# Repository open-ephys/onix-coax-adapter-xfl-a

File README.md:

# ONIX X.Coax Adapter Boards
Coaxial micro-tether interface for the following headstages and miniscopes

| Revision | Compatibility | Status |
|-|-|-|
| X.FL\rev1.0 | Headstage-64 | Produced and validated |
| X.FL\rev1.1 | Headstage-64 | Not produced |
| X.FL\rev1.2 | Headstage-64 | Produced and validated |
| X.FL\rev2.0 | Headstage-64s <br /> Headstage-16Stim <br /> Headstage-RHS2116 <br /> Kiloscope | Produced and validated |
| U.FL\rev1.0 | Headstage-64 | Not produced |

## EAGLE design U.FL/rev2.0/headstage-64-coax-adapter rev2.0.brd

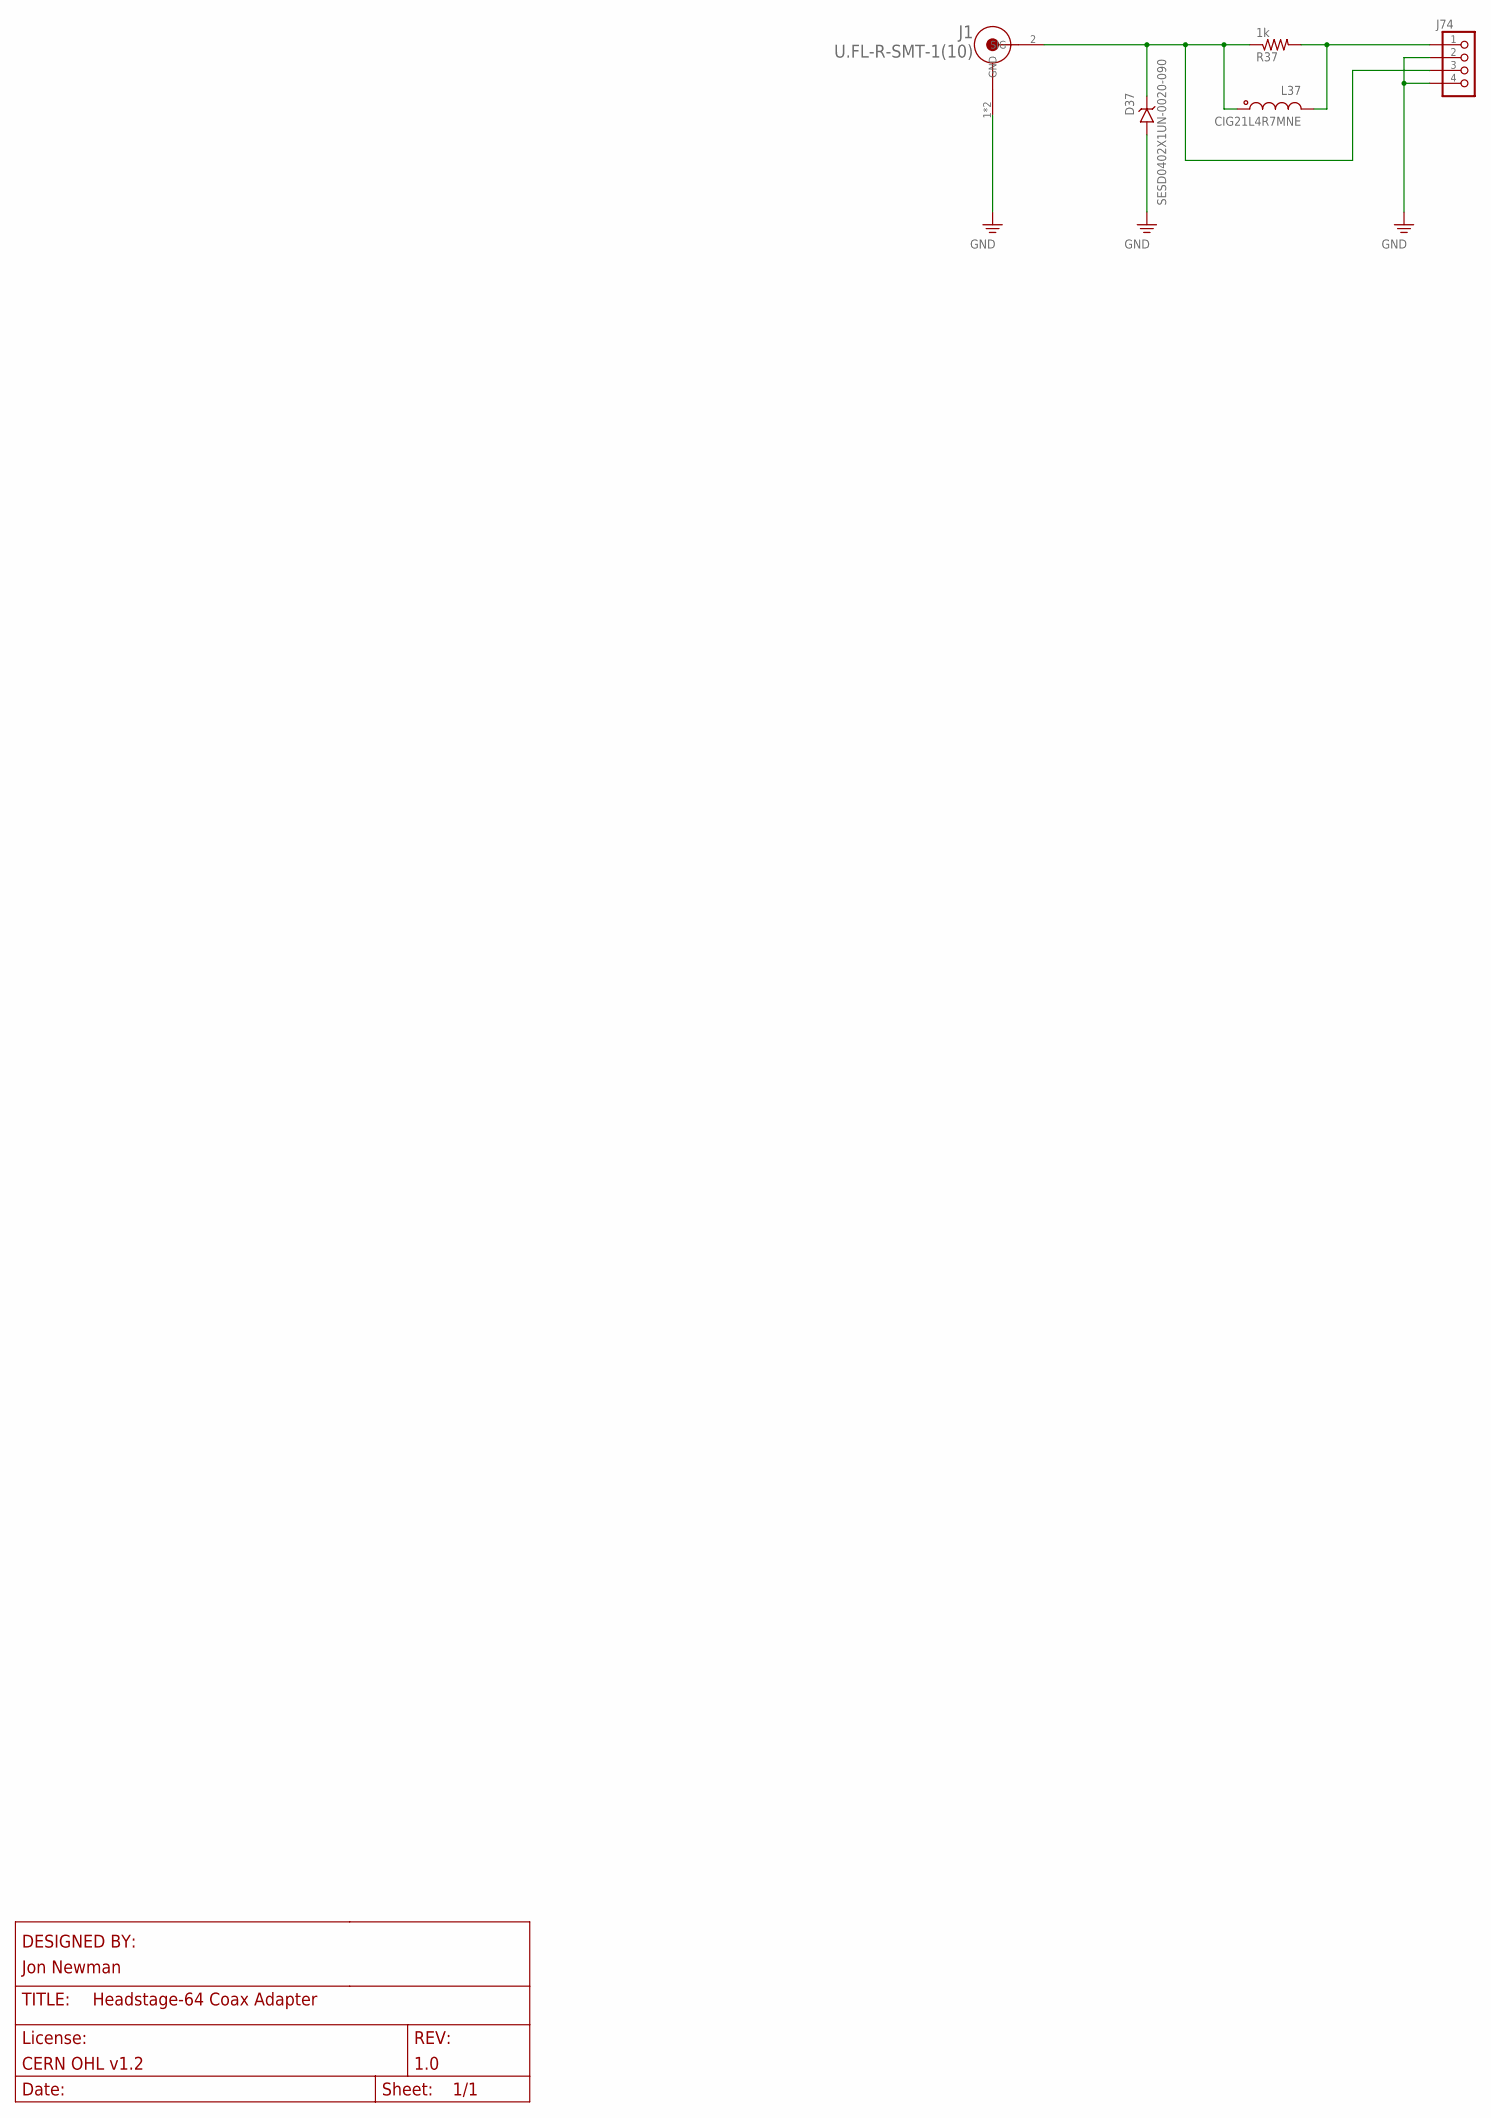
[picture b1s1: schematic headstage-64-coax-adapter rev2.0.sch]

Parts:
D37: SESD0402X1UN-0020-090; 0402T-DFN
J1: U.FL-R-SMT-1(10); HRS_U.FL-R-SMT-1(10)
J74: PINHD-1X4HEADSTAGE64-DAUGHTER-CARD-CASTELLATED; HEADSTAGE64-DAUGHER-CARD-CASTELLATED
L37: CIG21L4R7MNE; 0805T
R37: 1k; 0201T

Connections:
GND: D37.A, J1.1 (GND), J1.3 (GND), J74.2, J74.4
unnamed: J74.1, L37.2, R37.2
_SIGOUT37: D37.C, J1.2 (SIG), J74.3, L37.1, R37.1

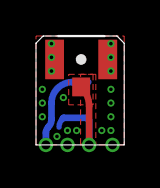
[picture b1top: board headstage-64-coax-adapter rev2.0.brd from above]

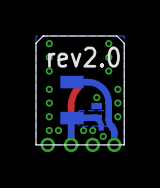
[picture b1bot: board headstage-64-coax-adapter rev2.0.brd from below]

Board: 4 copper layers, 4.9 x 6.0 mm, 5 parts (3 on the bottom side), 3 nets.

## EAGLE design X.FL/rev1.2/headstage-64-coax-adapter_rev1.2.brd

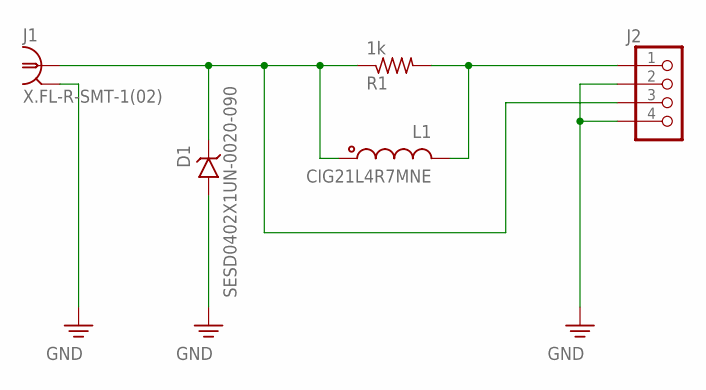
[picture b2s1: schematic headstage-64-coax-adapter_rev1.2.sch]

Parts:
D1: SESD0402X1UN-0020-090; 0402T-DFN
J1: X.FL-R-SMT-1(02); X_FL_R_SMT_1(02)
J2: PINHD-1X4HEADSTAGE64-DAUGHTER-CARD-CASTELLATED; HEADSTAGE64-DAUGHER-CARD-CASTELLATED
L1: CIG21L4R7MNE; 0805T
R1: 1k; 0201T

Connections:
GND: D1.A, J1.P$2 (2), J1.P$3 (2), J1.P$4 (2), J2.2, J2.4
unnamed: J2.1, L1.2, R1.2
_SIGOUT1: D1.C, J1.P$1 (1), J2.3, L1.1, R1.1

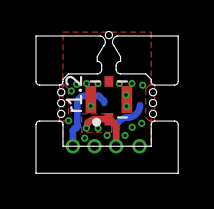
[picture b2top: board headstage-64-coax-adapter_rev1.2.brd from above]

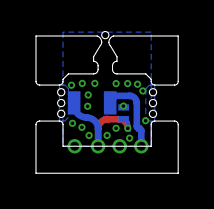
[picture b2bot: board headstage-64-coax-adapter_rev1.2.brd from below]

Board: 4 copper layers, 7.9 x 7.6 mm, 5 parts (3 on the bottom side), 3 nets.

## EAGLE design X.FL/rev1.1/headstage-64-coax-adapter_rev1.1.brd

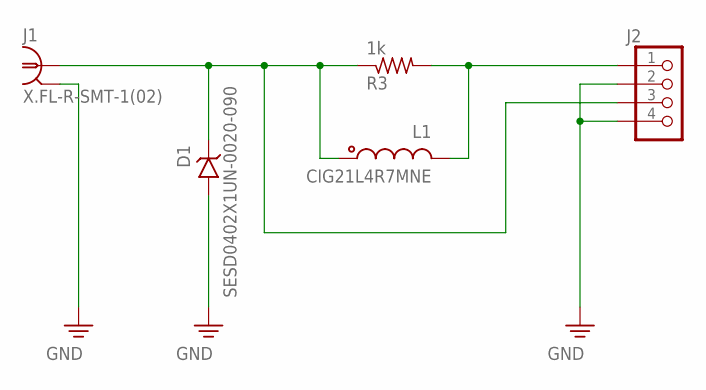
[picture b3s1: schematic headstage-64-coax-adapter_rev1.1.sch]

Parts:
D1: SESD0402X1UN-0020-090; 0402T-DFN
J1: X.FL-R-SMT-1(02); X_FL_R_SMT_1(02)
J2: PINHD-1X4HEADSTAGE64-DAUGHTER-CARD-CASTELLATED; HEADSTAGE64-DAUGHER-CARD-CASTELLATED
L1: CIG21L4R7MNE; 0805T
R3: 1k; 0201T

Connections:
GND: D1.A, J1.P$2 (2), J1.P$3 (2), J1.P$4 (2), J2.2, J2.4
unnamed: J2.1, L1.2, R3.2
_SIGOUT1: D1.C, J1.P$1 (1), J2.3, L1.1, R3.1

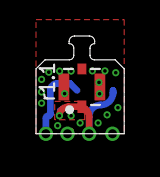
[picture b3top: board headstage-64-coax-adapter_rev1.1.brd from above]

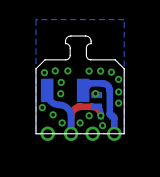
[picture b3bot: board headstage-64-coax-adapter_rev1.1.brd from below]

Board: 4 copper layers, 4.9 x 5.4 mm, 5 parts (3 on the bottom side), 3 nets.

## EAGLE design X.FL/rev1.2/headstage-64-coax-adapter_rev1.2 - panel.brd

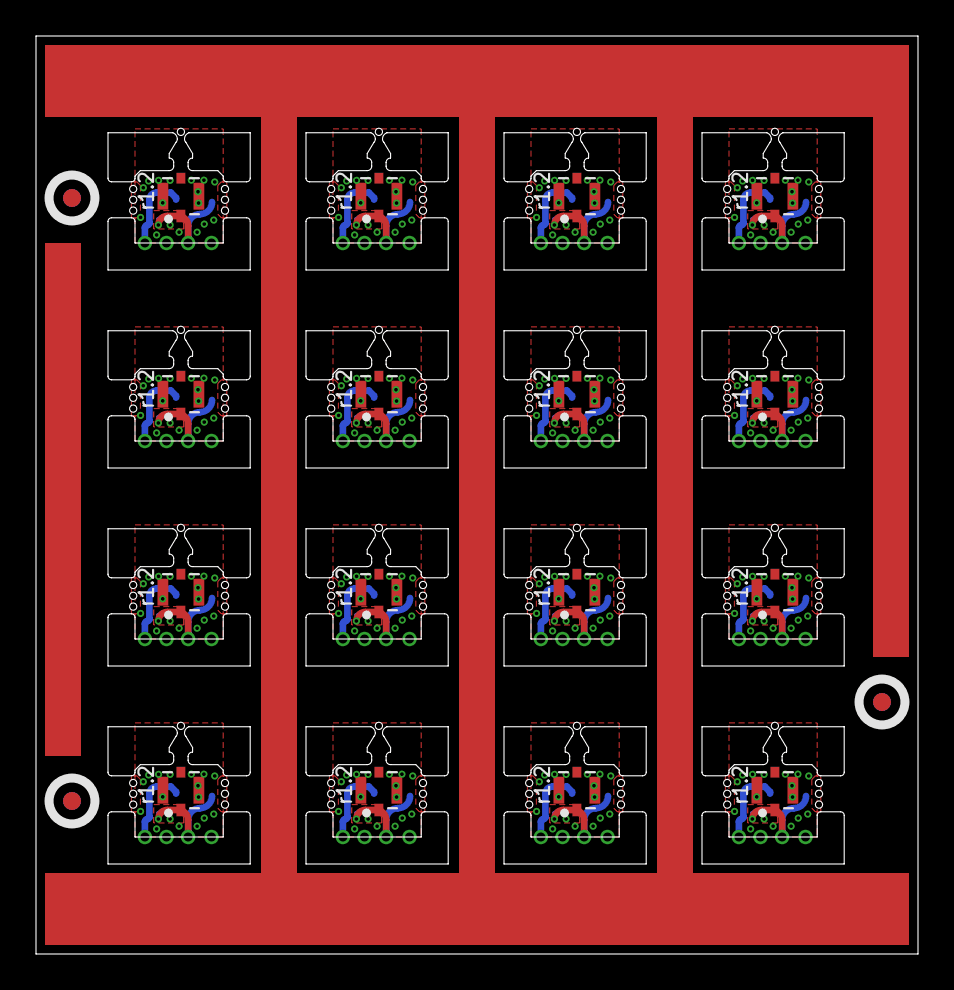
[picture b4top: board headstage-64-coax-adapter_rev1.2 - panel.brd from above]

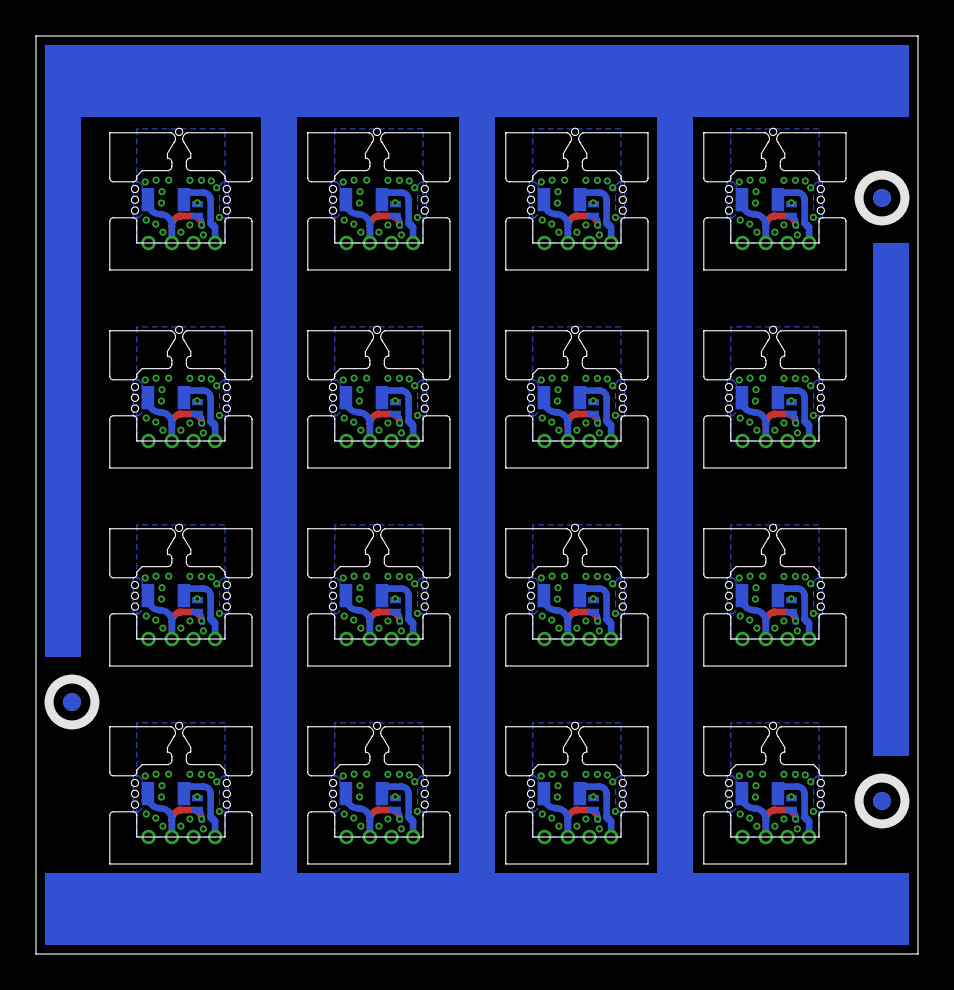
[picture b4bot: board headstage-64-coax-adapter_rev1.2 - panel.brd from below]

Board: 4 copper layers, 49.0 x 51.0 mm, 86 parts (51 on the bottom side), 48 nets.

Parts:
D1, D2, D3, D4, D5, D6, D7, D8, D9, D10, D11, D12, D13, D14, D15, D16: SESD0402X1UN-0020-090; 0402T-DFN
E$1, E$2, E$3, E$4, E$5, E$6: FIDUCIAL
J1, J3, J5, J7, J9, J11, J13, J15, J17, J19, J21, J23, J25, J27, J29, J31: X.FL-R-SMT-1(02); X_FL_R_SMT_1(02)
J2, J4, J6, J8, J10, J12, J14, J16, J18, J20, J22, J24, J26, J28, J30, J32: HEADSTAGE64-DAUGHER-CARD-CASTELLATED
L1, L2, L3, L4, L5, L6, L7, L8, L9, L10, L11, L12, L13, L14, L15, L16: CIG21L4R7MNE; 0805T
R1, R2, R3, R4, R5, R6, R7, R8, R9, R10, R11, R12, R13, R14, R15, R16: 1k; 0201T

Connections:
GND: D1.A, J1.P$2, J1.P$3, J1.P$4, J2.2, J2.4
GND2: D2.A, J3.P$2, J3.P$3, J3.P$4, J4.2, J4.4
GND10: D3.A, J5.P$2, J5.P$3, J5.P$4, J6.2, J6.4
GND12: D4.A, J7.P$2, J7.P$3, J7.P$4, J8.2, J8.4
GND14: D5.A, J9.P$2, J9.P$3, J9.P$4, J10.2, J10.4
GND16: D6.A, J11.P$2, J11.P$3, J11.P$4, J12.2, J12.4
GND18: D7.A, J13.P$2, J13.P$3, J13.P$4, J14.2, J14.4
GND20: D8.A, J15.P$2, J15.P$3, J15.P$4, J16.2, J16.4
GND22: D9.A, J17.P$2, J17.P$3, J17.P$4, J18.2, J18.4
GND24: D10.A, J19.P$2, J19.P$3, J19.P$4, J20.2, J20.4
GND26: D11.A, J21.P$2, J21.P$3, J21.P$4, J22.2, J22.4
GND28: D12.A, J23.P$2, J23.P$3, J23.P$4, J24.2, J24.4
GND30: D13.A, J25.P$2, J25.P$3, J25.P$4, J26.2, J26.4
GND32: D14.A, J27.P$2, J27.P$3, J27.P$4, J28.2, J28.4
GND34: D15.A, J29.P$2, J29.P$3, J29.P$4, J30.2, J30.4
GND36: D16.A, J31.P$2, J31.P$3, J31.P$4, J32.2, J32.4
unnamed: J4.1, L2.2, R1.2
unnamed: J6.1, L3.2, R2.2
unnamed: J8.1, L4.2, R4.2
unnamed: J10.1, L5.2, R5.2
unnamed: J12.1, L6.2, R6.2
unnamed: J14.1, L7.2, R7.2
unnamed: J16.1, L8.2, R8.2
unnamed: J18.1, L9.2, R9.2
unnamed: J20.1, L10.2, R10.2
unnamed: J22.1, L11.2, R11.2
unnamed: J24.1, L12.2, R12.2
unnamed: J26.1, L13.2, R13.2
unnamed: J28.1, L14.2, R14.2
unnamed: J30.1, L15.2, R15.2
unnamed: J32.1, L16.2, R16.2
unnamed: J2.1, L1.2, R3.2
_SIGOUT1: D1.C, J1.P$1, J2.3, L1.1, R3.1
_SIGOUT2: D2.C, J3.P$1, J4.3, L2.1, R1.1
_SIGOUT3: D3.C, J5.P$1, J6.3, L3.1, R2.1
_SIGOUT4: D4.C, J7.P$1, J8.3, L4.1, R4.1
_SIGOUT5: D5.C, J9.P$1, J10.3, L5.1, R5.1
_SIGOUT6: D6.C, J11.P$1, J12.3, L6.1, R6.1
_SIGOUT7: D7.C, J13.P$1, J14.3, L7.1, R7.1
_SIGOUT8: D8.C, J15.P$1, J16.3, L8.1, R8.1
_SIGOUT9: D9.C, J17.P$1, J18.3, L9.1, R9.1
_SIGOUT10: D10.C, J19.P$1, J20.3, L10.1, R10.1
_SIGOUT11: D11.C, J21.P$1, J22.3, L11.1, R11.1
_SIGOUT12: D12.C, J23.P$1, J24.3, L12.1, R12.1
_SIGOUT13: D13.C, J25.P$1, J26.3, L13.1, R13.1
_SIGOUT14: D14.C, J27.P$1, J28.3, L14.1, R14.1
_SIGOUT15: D15.C, J29.P$1, J30.3, L15.1, R15.1
_SIGOUT16: D16.C, J31.P$1, J32.3, L16.1, R16.1

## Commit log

2022-12-29 Moved current design to X.FL\rev2.0
    The current designed is considered to be revision 2.0.
2022-12-29 Added the very first version (rev1.0).
    This version was designed by @jonnew to interface with the first version of the ONIX Headstage-64
2022-12-29 Added rev1.1.
    This version was not used.
2022-12-29 Added rev1.2.
2022-12-29 Added the first attempt of using an U.FL connector.
2022-12-29 Added compatibility table.

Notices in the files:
U.FL/rev2.0/headstage-64-coax-adapter rev2.0.sch:
LICENSE: CERN OHL v1.2
